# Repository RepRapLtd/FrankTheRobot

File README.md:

This is a small robot for testing out LIDAR scanning rangefinders, automatic environment mapping, 21st century Grey-Walter tortoise like behaviour etc.

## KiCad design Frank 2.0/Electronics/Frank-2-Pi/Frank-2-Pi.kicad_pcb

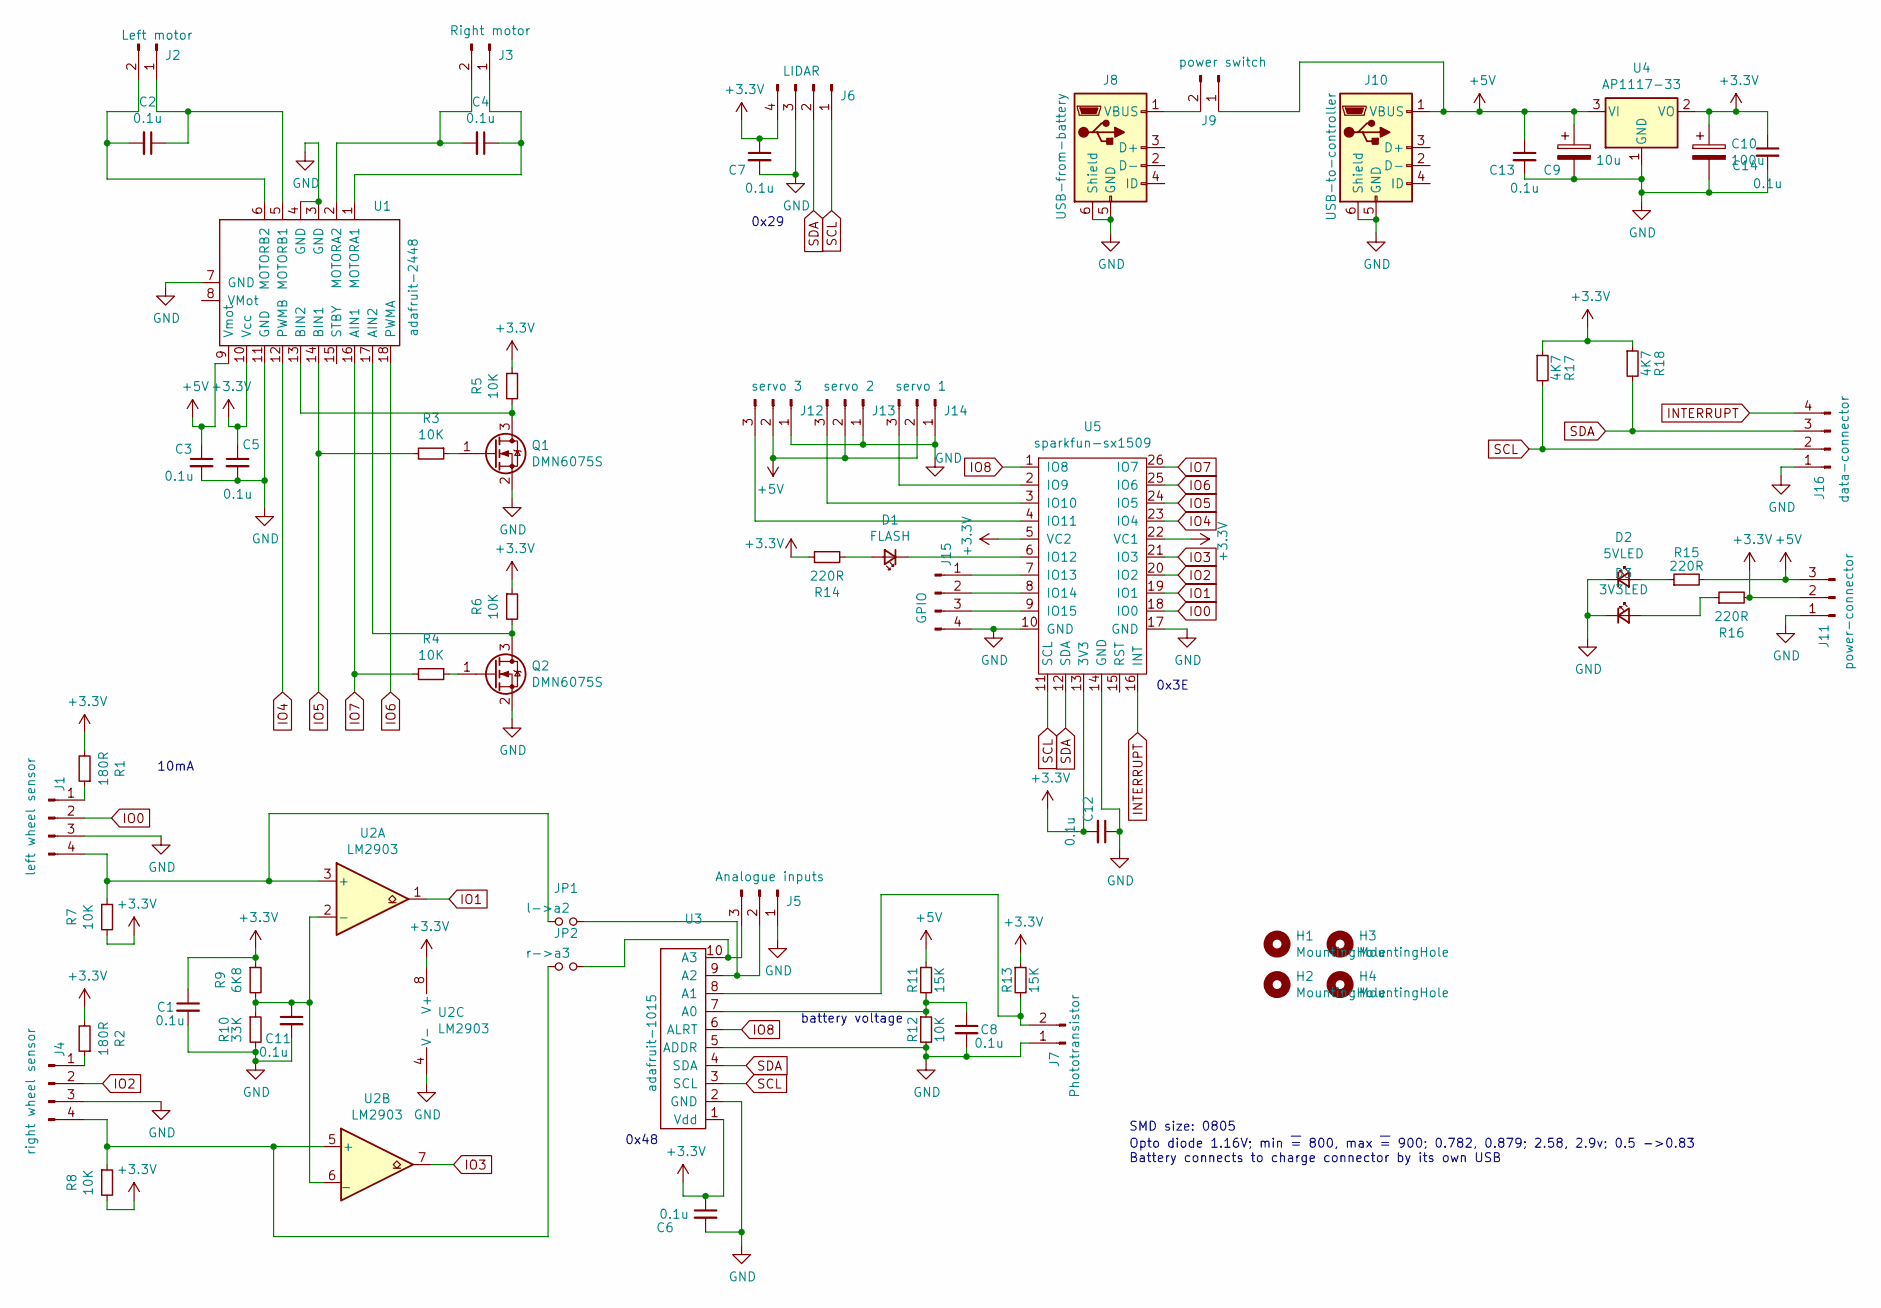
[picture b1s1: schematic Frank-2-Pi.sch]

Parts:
C1, C2, C3, C4, C5, C6, C7, C8, C11, C12, C13, C14: 0.1u; C_0805_2012Metric
C9: 10u; CP_EIA-3216-18_Kemet-A_Pad1.58x1.35mm_HandSolder
C10: 100u; CP_EIA-3216-18_Kemet-A_Pad1.58x1.35mm_HandSolder
D1: FLASH; LED_D3.0mm
D2: 5VLED; LED_D3.0mm
D3: 3V3LED; LED_D3.0mm
H1, H2, H3, H4: MountingHole; MountingHole_3.2mm_M3
J1: left wheel sensor; PinHeader_1x04_P2.54mm_Vertical
J2: Left motor; PinHeader_1x02_P2.54mm_Vertical
J3: Right motor; PinHeader_1x02_P2.54mm_Vertical
J4: right wheel sensor; PinHeader_1x04_P2.54mm_Vertical
J5: Analogue inputs; PinHeader_1x03_P2.54mm_Vertical
J6: LIDAR; PinHeader_1x04_P2.54mm_Vertical
J7: Phototransistor; PinHeader_1x02_P2.54mm_Vertical
J8: USB-from-battery; USB_Micro-B_Wuerth_629105150521
J9: power switch; PinHeader_1x02_P2.54mm_Vertical
J10: USB-to-controller; USB_Micro-B_Wuerth_629105150521
J11: power-connector; PinHeader_1x03_P2.54mm_Vertical
J12: servo 3; PinHeader_1x03_P2.54mm_Vertical
J13: servo 2; PinHeader_1x03_P2.54mm_Vertical
J14: servo 1; PinHeader_1x03_P2.54mm_Vertical
J15: GPIO; PinHeader_1x04_P2.54mm_Vertical
J16: data-connector; PinHeader_1x04_P2.54mm_Vertical
JP1: l->a2; SolderJumper-2_P1.3mm_Open_RoundedPad1.0x1.5mm
JP2: r->a3; SolderJumper-2_P1.3mm_Open_RoundedPad1.0x1.5mm
Q1, Q2: DMN6075S; SOT-23
R1, R2: 180R; R_0805_2012Metric
R3, R4, R5, R6, R7, R8, R12: 10K; R_0805_2012Metric
R9: 6K8; R_0805_2012Metric
R10: 33K; R_0805_2012Metric
R11, R13: 15K; R_0805_2012Metric
R14, R15, R16: 220R; R_0805_2012Metric
R17, R18: 4K7; R_0805_2012Metric
U1: adafruit-2448
U2: LM2903; Diodes_SO-8EP
U3: adafruit-1015
U4: AP1117-33; SOT-223-3_TabPin2
U5: sparkfun-sx1509

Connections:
+3V3: C1.1, C5.1, C6.1, C7.1, C10.1, C12.2, C14.1, J6.4, J11.2, R1.2, R2.2, R5.1, R6.1, R7.2, R8.2, R9.1, R13.1, R14.1, R16.2, R17.1, R18.1, U1.10 (Vcc), U2.8 (V+), U3.1 (Vdd), U4.2 (VO), U5.5 (VC2), U5.13 (3V3), U5.22 (VC1)
+5V: C3.1, C9.1, C13.1, J9.1, J10.1 (VBUS), J11.3, J12.2, J13.2, J14.2, R11.1, R15.2, U1.9 (Vmot), U4.3 (VI)
GND: C1.2, C3.2, C5.2, C6.2, C7.2, C8.2, C9.2, C10.2, C11.2, C12.1, C13.2, C14.2, D2.1 (K), D3.1 (K), J1.3, J4.3, J5.1, J6.3, J7.1, J8.5 (GND), J8.6 (Shield), J10.5 (GND), J10.6 (Shield), J11.1, J12.1, J13.1, J14.1, J15.4, J16.1, Q1.2 (S), Q2.2 (S), R10.2, R12.2, U1.3 (GND), U1.4 (GND), U1.7 (GND), U1.11 (GND), U2.4 (V-), U3.2 (GND), U3.5 (ADDR), U4.1 (GND), U5.10 (GND), U5.14 (GND), U5.17 (GND)
INTERRUPT: J16.4, U5.16 (INT)
IO0: J1.2, U5.18 (IO0)
IO1: U2.1, U5.19 (IO1)
IO2: J4.2, U5.20 (IO2)
IO3: U2.7, U5.21 (IO3)
IO4: U1.12 (PWMB), U5.23 (IO4)
IO5: R3.2, U1.14 (BIN1), U5.24 (IO5)
IO6: U1.18 (PWMA), U5.25 (IO6)
IO7: R4.2, U1.16 (AIN1), U5.26 (IO7)
IO8: U3.6 (ALRT), U5.1 (IO8)
unnamed: C2.1, J2.1, U1.5 (MOTORB1)
unnamed: C2.2, J2.2, U1.6 (MOTORB2)
unnamed: C4.1, J3.1, U1.1 (MOTORA1)
unnamed: C4.2, J3.2, U1.2 (MOTORA2)
unnamed: C8.1, R11.2, R12.1, U3.7 (A0)
unnamed: C11.1, R9.2, R10.1, U2.2 (-), U2.6 (_)
unnamed: D1.1 (K), U5.6 (IO12)
unnamed: D1.2 (A), R14.2
unnamed: D2.2 (A), R15.1
unnamed: D3.2 (A), R16.1
unnamed: J1.1, R1.1
unnamed: J1.4, JP1.1, R7.1, U2.3 (+)
unnamed: J4.1, R2.1
unnamed: J4.4, JP2.1, R8.1, U2.5 (+)
unnamed: J5.2, JP1.2, U3.9 (A2)
unnamed: J5.3, JP2.2, U3.10 (A3)
unnamed: J7.2, R13.2, U3.8 (A1)
unnamed: J8.1 (VBUS), J9.2
unnamed: J12.3, U5.4 (IO11)
unnamed: J13.3, U5.3 (IO10)
unnamed: J14.3, U5.2 (IO9)
unnamed: J15.1, U5.7 (IO13)
unnamed: J15.2, U5.8 (IO14)
unnamed: J15.3, U5.9 (IO15)
unnamed: Q1.1 (G), R3.1
unnamed: Q1.3 (D), R5.2, U1.13 (BIN2)
unnamed: Q2.1 (G), R4.1
unnamed: Q2.3 (D), R6.2, U1.17 (AIN2)
SCL: J6.1, J16.2, R17.2, U3.3 (SCL), U5.11 (SCL)
SDA: J6.2, J16.3, R18.2, U3.4 (SDA), U5.12 (SDA)

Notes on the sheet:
SMD size: 0805
Opto diode 1.16V; min ~= 800, max ~= 900; 0.782, 0.879; 2.58, 2.9v; 0.5 ->0.83 Battery connects to charge connector by its own USB
10mA
battery voltage
0x29
0x3E
0x48

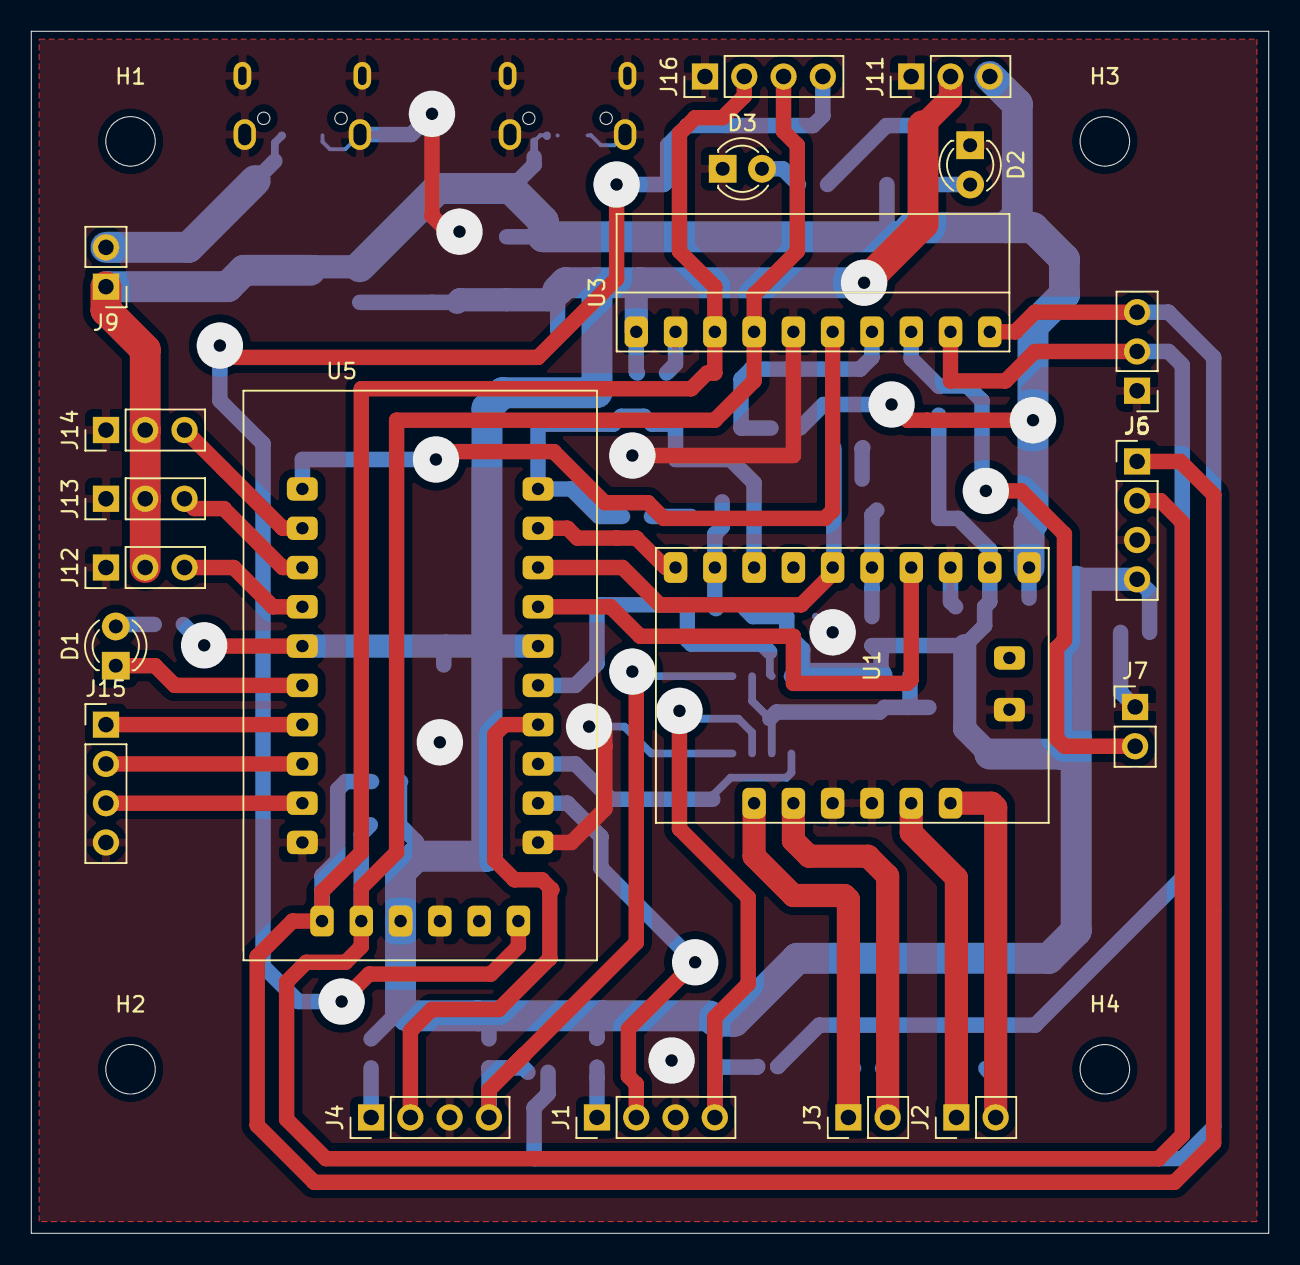
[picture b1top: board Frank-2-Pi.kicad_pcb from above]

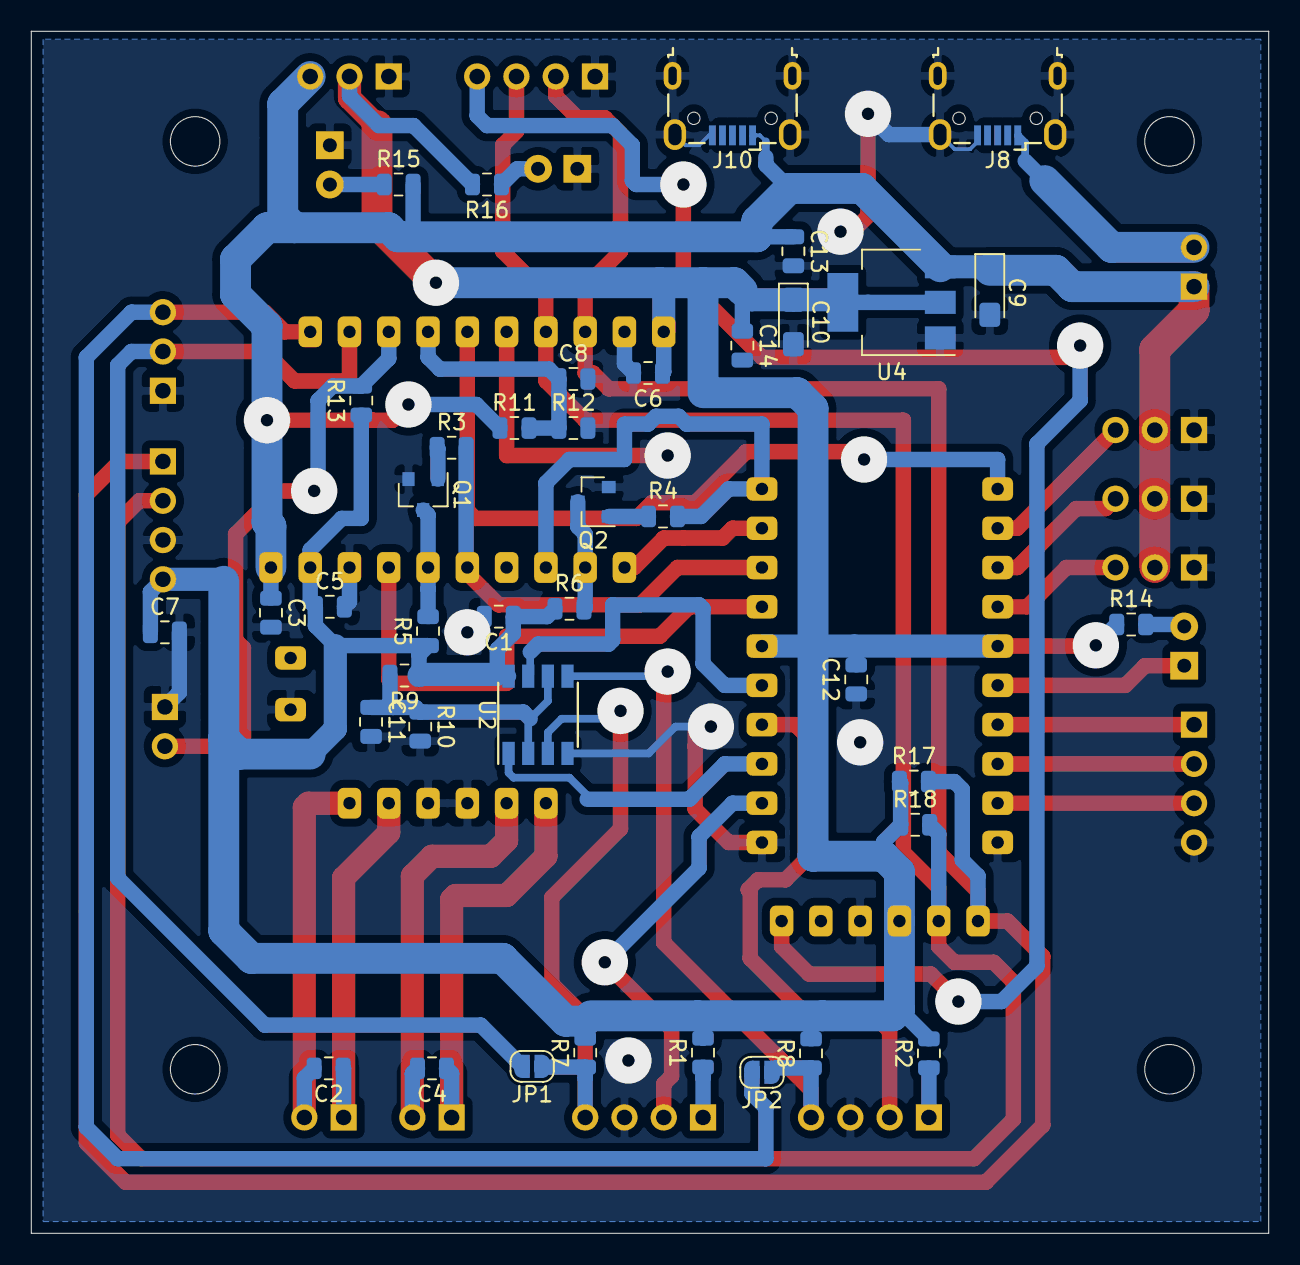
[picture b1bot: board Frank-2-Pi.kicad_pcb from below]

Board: 2 copper layers, 80.0 x 77.7 mm, 64 parts (40 on the bottom side), 43 nets.

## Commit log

2017-12-18 New software that behaves sensibly with obstacles.
2017-12-19 1st hack at the shield design for WiFi Frank...
2017-12-21 Improved shield design. GERBER files added.
2017-12-21 Just testing the clean function...
2018-01-04 Added opposite rotation on bump and additional "wiggle" scan every 10 secs
2018-01-08 Added Frank's picture...
    Also Sally w.i.p. on the WiFi version.
2018-01-31 Updated electronics to power the wheel sensors directly off the battery. (They take too much current from 3V3 if that is used; the sensors now have potential dividers so their output never exceeds 3v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
    Added a PCB test program for the Wemos D1/ESP8266 board (W.I.P.)
2018-02-01 Increased diameter of optosensor vias to make them easier to mill.
2018-02-01 Added LED to shield, and anti-short safety diode to the charge circuit.
2018-05-11 PCBs corrected (D9 now LED) and improved (wheel sensor has 4 mounting holes); software updated to match.
2018-06-08 PCB test program updated; all works.
    TODO: write motor callibration function
    update schematic and PCB to take account of the use of the
    LED pin for input
2018-06-11 Caution update...
2018-06-20 Wemos MINI PCB added. Corrections to battery holder W.I.P.
2018-06-24 Sally's design mods.
2019-01-25 Added phototransistor 665-5347 to schematic.
2019-01-30 File tidying.
2019-05-20 Latest control prog (0.3) W.I.P.
2019-05-22 Compiles without errors...
2020-05-19 Starting work on Frank 2.0.
    Shaft opto encoder and motor/voltage speed experiment.
2020-05-20 Electronics for Frank 2.0 WIP.
2020-05-21 Frank 2 electronics WIP.
2020-05-22 Frank 2.0 electronics WIP.
2020-05-22 Now with indicator LEDs...
2020-05-25 Electronics WIP
2020-05-26 PCB WIP
2020-05-27 PCB finished (but probably not final...) Except for silks
2020-07-03 Updating lots of Frank 2.0 stuff...
2020-07-30 Improved motor mount and sensor. Improved motor test program.
2020-07-31 Improved motor test program WIP.
2020-08-03 Improved motor test program now working.
2020-08-12 Motor and castor design improvements. I2C pullup resistors added.
2020-09-02 Updated s/w and PCB
2021-03-25 PCB as prototyped.
2024-05-29 Updating
